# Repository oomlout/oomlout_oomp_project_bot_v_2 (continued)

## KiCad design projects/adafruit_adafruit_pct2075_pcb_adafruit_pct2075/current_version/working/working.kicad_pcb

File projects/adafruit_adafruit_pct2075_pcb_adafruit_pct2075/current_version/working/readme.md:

# adafruit_pct2075_pcb
 
## summary 
* id: adafruit_adafruit_pct2075_pcb_adafruit_pct2075
* user: adafruit
* name: adafruit_pct2075_pcb
* board: adafruit_pct2075
* repo: https://github.com/adafruit/Adafruit-PCT2075-PCB

* src_file_repo_sch: 
* src_file_repo_sch_link: https://github.com/adafruit/Adafruit-PCT2075-PCB/tree/master/
* full details link: https://github.com/oomlout/oomlout_oomp_project_bot_v_2/tree/main/projects/adafruit_adafruit_pct2075_pcb_adafruit_pct2075/current_version/working  

## schematic  
  
[schematic (pdf)](working_schematic.pdf) 

## pcb  

[board (pdf)](working.pdf)  

## working_bom
| Id | Designator | Footprint | Quantity | Designation | Supplier and ref |  | None | 
| --- | --- | --- | --- | --- | --- | --- | --- | 
| 1 | R3 | RESPACK_4X0603 | 1 | 10K |  |  | [''] | 
| 2 | JP3 | 1X05_ROUND | 1 |  |  |  | [''] | 
| 3 | FID4,FID3 | FIDUCIAL_1MM | 2 | FIDUCIAL_1MM |  |  | [''] | 
| 4 | U$19,U$1,U$17,U$21 | MOUNTINGHOLE_2.5_PLATED | 4 | MOUNTINGHOLE2.5 |  |  | [''] | 
| 5 | U$22 | ADAFRUIT_3.5MM | 1 |  |  |  | [''] | 
| 6 | C2 | 0805-NO | 1 | 10uF |  |  | [''] | 
| 7 | CONN4,CONN3 | JST_SH4 | 2 | STEMMA_I2C_QT |  |  | [''] | 
| 8 | C1 | 0603-NO | 1 | 0.1uF |  |  | [''] | 
| 9 | U$2 | SOIC8_150MIL | 1 | PCT2075D |  |  | [''] | 
| 10 | D1 | CHIPLED_0603_NOOUTLINE | 1 | GREEN |  |  | [''] | 
| 11 | JP2 | 1X03_ROUND | 1 |  |  |  | [''] | 
| 12 | SJ6,SJ4,SJ5 | SOLDERJUMPER_2WAY_OPEN_NOPASTE | 3 |  |  |  | [''] | 
| 13 | U$30,U$31 | STEMMAQT | 2 |  |  |  | [''] | 
| 14 | U$25 | PCBFEAT-REV-040 | 1 |  |  |  | [''] | 

## bom_schematic
| Ref | Qnty | Value | Cmp name | Footprint | Description | Vendor | DNP | 
| --- | --- | --- | --- | --- | --- | --- | --- | 
| C1 | 1 | 0.1uF | CAP_CERAMIC0603_NO | working:0603-NO |  |  |  | 
| C2 | 1 | 10uF | CAP_CERAMIC0805-NOOUTLINE | working:0805-NO |  |  |  | 
| CONN3, CONN4 | 2 | STEMMA_I2C_QT | STEMMA_I2C_QT | working:JST_SH4 |  |  |  | 
| D1 | 1 | GREEN | LED0603_NOOUTLINE | working:CHIPLED_0603_NOOUTLINE |  |  |  | 
| FID3, FID4 | 2 | FIDUCIAL_1MM | FIDUCIAL_1MM | working:FIDUCIAL_1MM |  |  |  | 
| JP2 | 1 | HEADER-1X3ROUND | HEADER-1X3ROUND | working:1X03_ROUND |  |  |  | 
| JP3 | 1 | HEADER-1X5ROUND | HEADER-1X5ROUND | working:1X05_ROUND |  |  |  | 
| R3 | 1 | 10K | RESISTOR_4PACK | working:RESPACK_4X0603 |  |  |  | 
| SJ4, SJ5, SJ6 | 3 | SOLDERJUMPER_2WAY | SOLDERJUMPER_2WAY | working:SOLDERJUMPER_2WAY_OPEN_NOPASTE |  |  |  | 
| U$1, U$17, U$19, U$21 | 4 | MOUNTINGHOLE2.5 | MOUNTINGHOLE2.5 | working:MOUNTINGHOLE_2.5_PLATED |  |  |  | 
| U$2 | 1 | PCT2075D | PCT2075D | working:SOIC8_150MIL |  |  |  | 

## mounting_holes
| x | y | package | value | ref | size | 
| --- | --- | --- | --- | --- | --- | 
| 0.0 | 12.7 | MOUNTINGHOLE_2.5_PLATED | MOUNTINGHOLE2.5 | U$1 | m3 | 
| 20.32 | 12.7 | MOUNTINGHOLE_2.5_PLATED | MOUNTINGHOLE2.5 | U$17 | m3 | 
| 0.0 | 0.0 | MOUNTINGHOLE_2.5_PLATED | MOUNTINGHOLE2.5 | U$19 | m3 | 
| 20.32 | 0.0 | MOUNTINGHOLE_2.5_PLATED | MOUNTINGHOLE2.5 | U$21 | m3 |

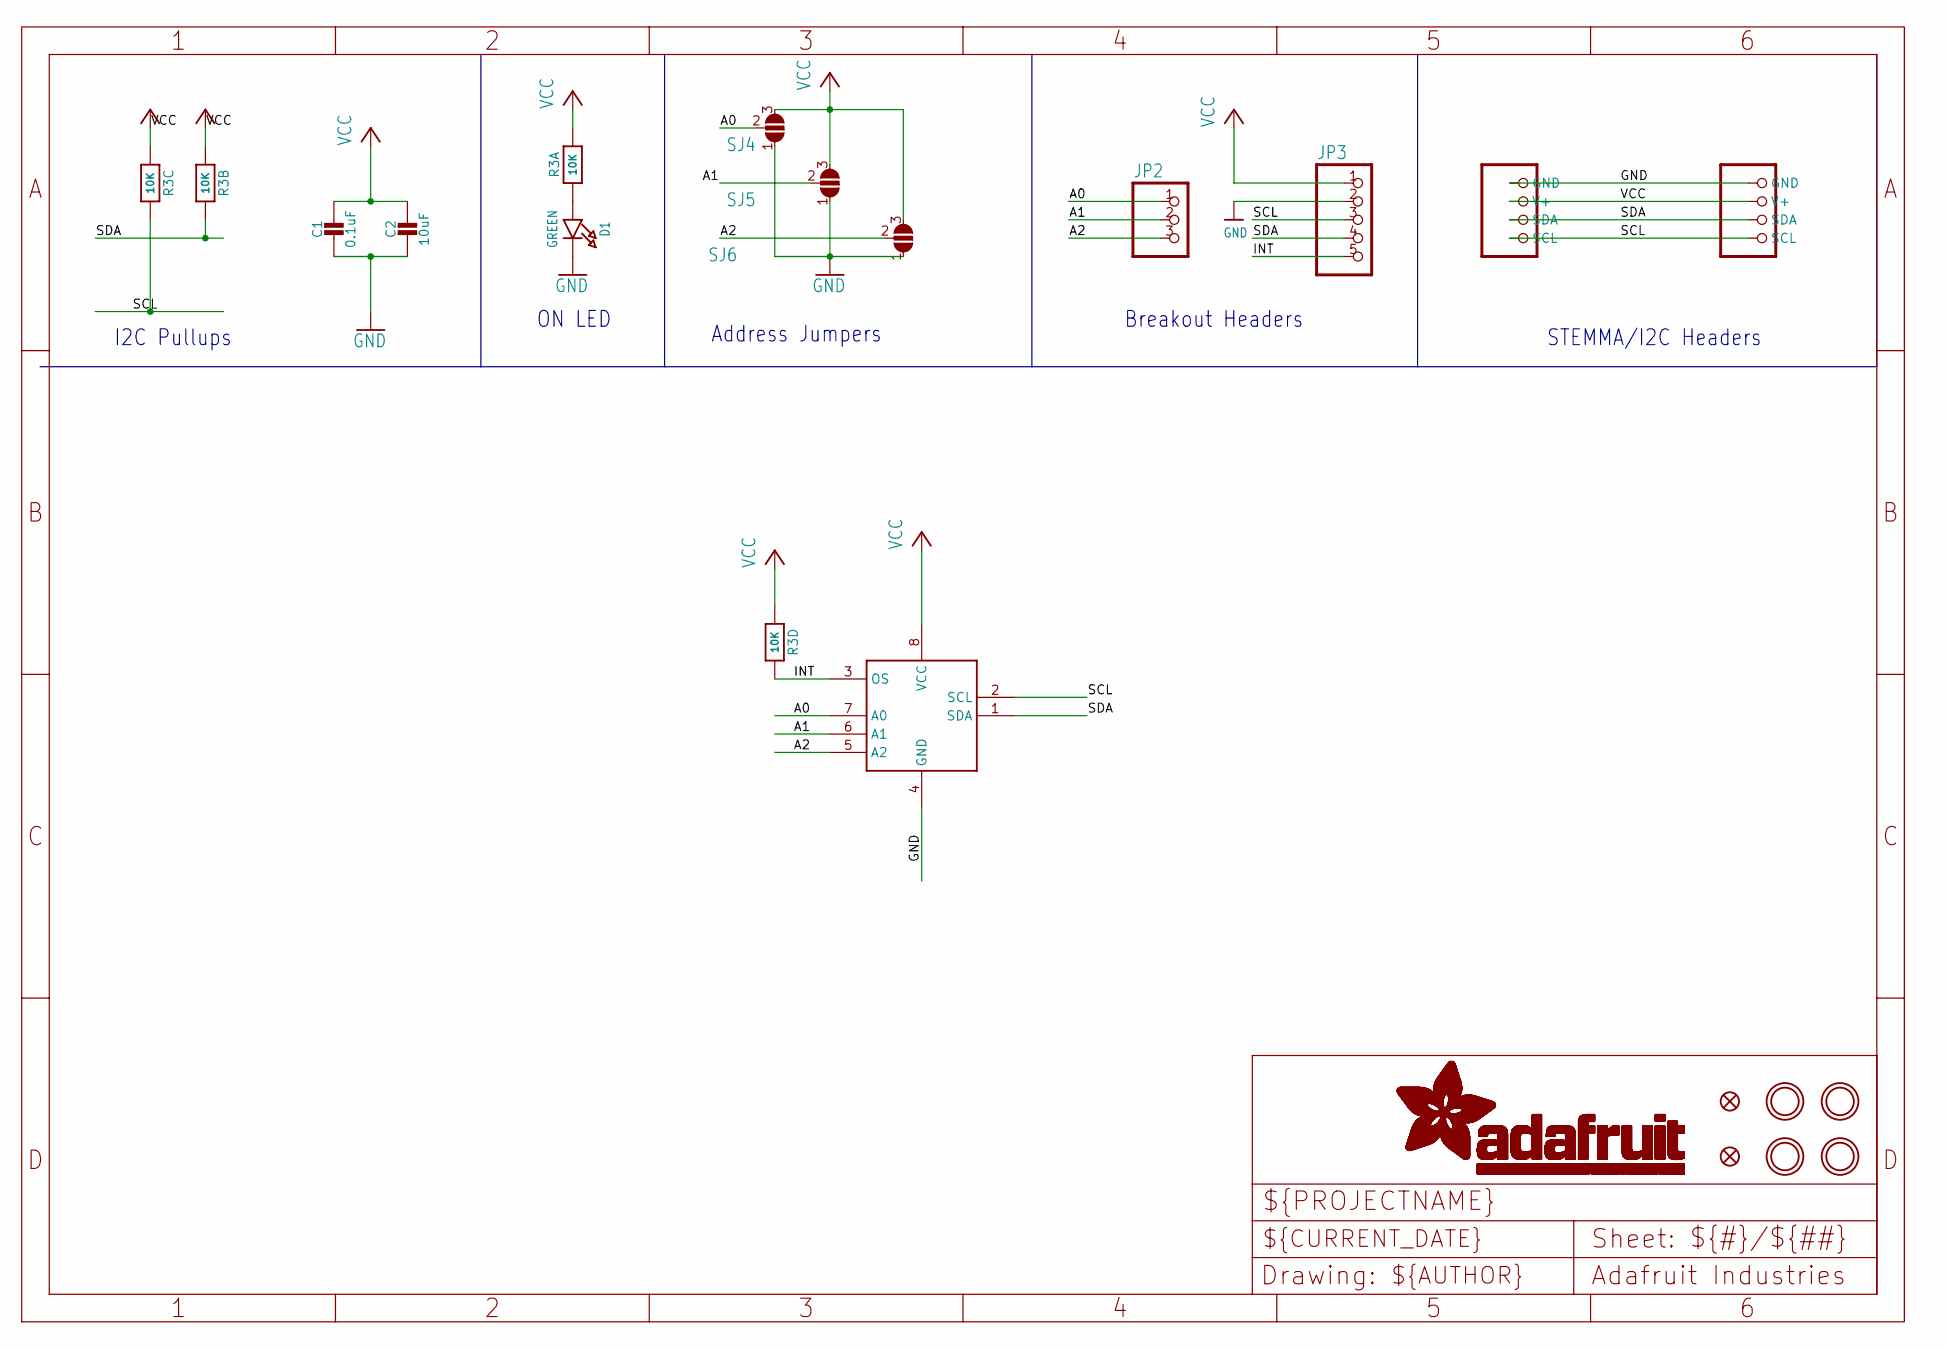
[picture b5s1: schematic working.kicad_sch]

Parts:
C1: 0.1uF; 0603-NO
C2: 10uF; 0805-NO
CONN3, CONN4: STEMMA_I2C_QT; JST_SH4
D1: GREEN; CHIPLED_0603_NOOUTLINE
FID3, FID4: FIDUCIAL_1MM
JP2: HEADER-1X3ROUND; 1X03_ROUND
JP3: HEADER-1X5ROUND; 1X05_ROUND
R3: 10K; RESPACK_4X0603
SJ4, SJ5, SJ6: SOLDERJUMPER_2WAY; SOLDERJUMPER_2WAY_OPEN_NOPASTE
U$1, U$17, U$19, U$21: MOUNTINGHOLE2.5; MOUNTINGHOLE_2.5_PLATED
U$2: PCT2075D; SOIC8_150MIL

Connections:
A0: JP2.1, SJ4.2, U$2.7 (A0)
A1: JP2.2, SJ5.2, U$2.6 (A1)
A2: JP2.3, SJ6.2, U$2.5 (A2)
GND: C1.2, C2.2, CONN3.1 (GND), CONN4.1 (GND), D1.C, JP3.2, SJ4.1, SJ5.1, SJ6.1, U$2.4 (GND)
INT: JP3.5, R3.5 (2), U$2.3 (OS)
unnamed: D1.A, R3.1
SCL: CONN3.4 (SCL), CONN4.4 (SCL), JP3.3, R3.6 (2), U$2.2 (SCL)
SDA: CONN3.3 (SDA), CONN4.3 (SDA), JP3.4, R3.7 (2), U$2.1 (SDA)
VCC: C1.1, C2.1, CONN3.2 (V+), CONN4.2 (V+), JP3.1, R3.2 (1), R3.3 (1), R3.4 (1), R3.8 (2), SJ4.3, SJ5.3, SJ6.3, U$2.8 (VCC)

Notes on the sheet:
I2C Pullups
ON LED
Breakout Headers
STEMMA/I2C Headers
Address Jumpers

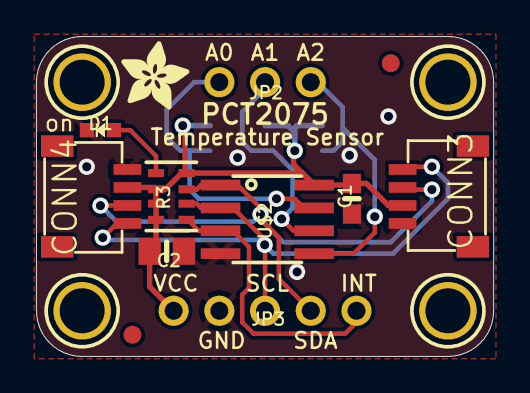
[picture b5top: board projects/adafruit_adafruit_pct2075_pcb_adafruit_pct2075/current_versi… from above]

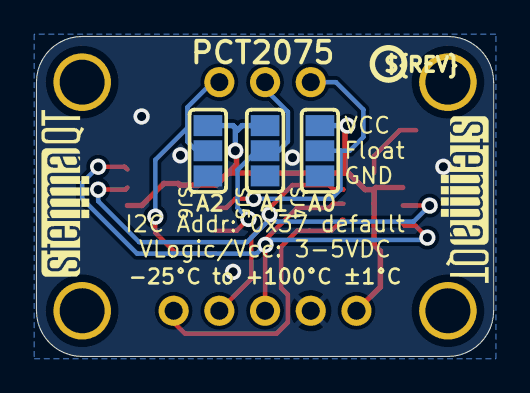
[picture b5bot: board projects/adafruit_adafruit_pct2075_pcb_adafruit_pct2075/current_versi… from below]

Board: 2 copper layers, 25.4 x 17.8 mm, 22 parts (6 on the bottom side), 9 nets.

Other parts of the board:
U$22: ADAFRUIT_3.5MM
U$25: PCBFEAT-REV-040
U$30, U$31: STEMMAQT
